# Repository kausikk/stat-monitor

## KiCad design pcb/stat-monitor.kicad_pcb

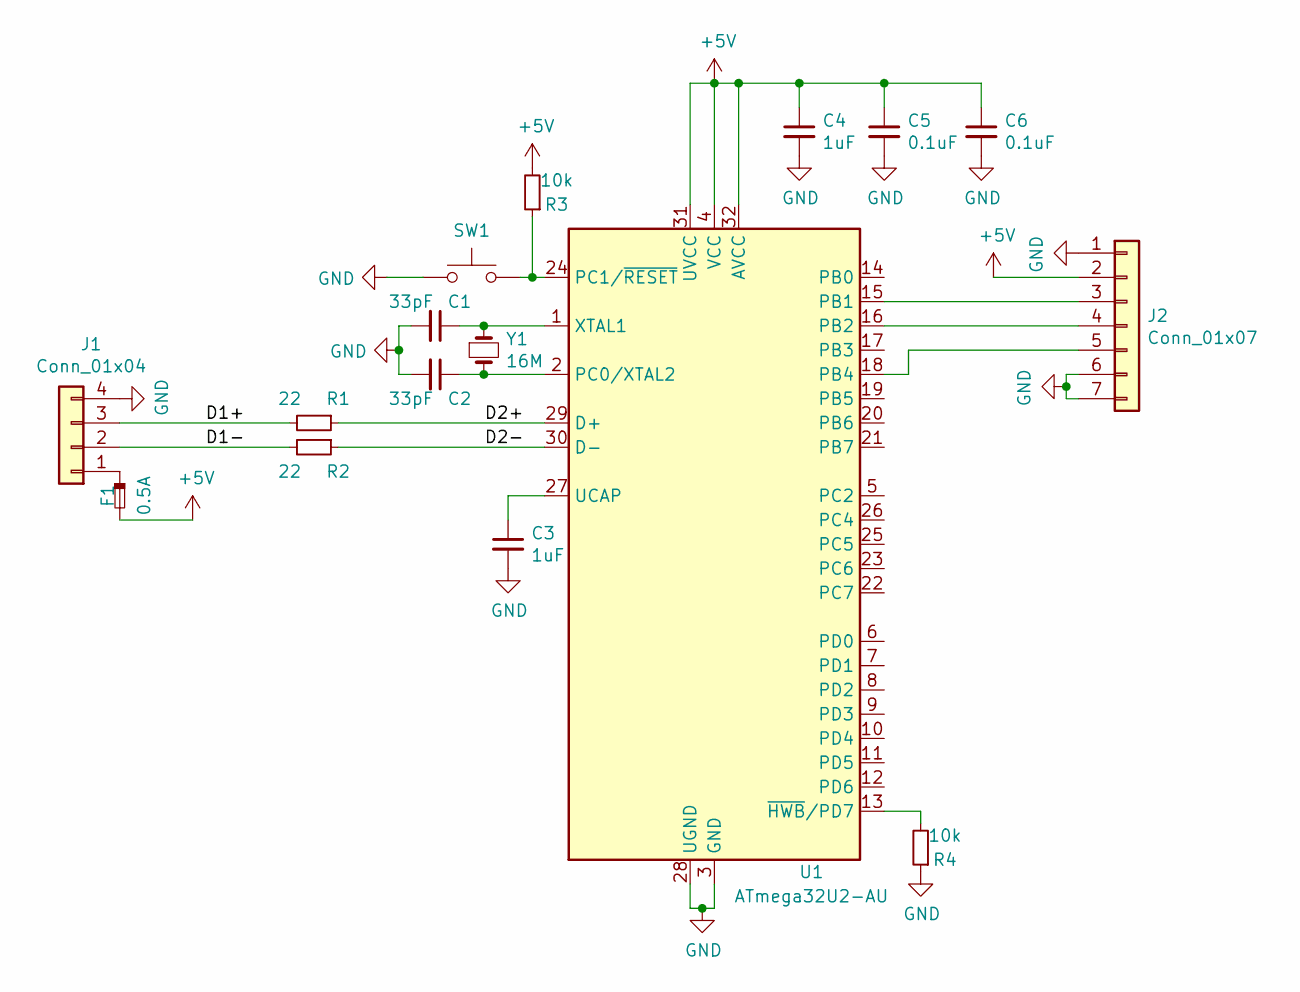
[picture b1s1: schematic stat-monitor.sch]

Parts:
C1, C2: 33pF; C_0603_1608Metric_Pad1.08x0.95mm_HandSolder
C3, C4: 1uF; C_0603_1608Metric_Pad1.08x0.95mm_HandSolder
C5, C6: 0.1uF; C_0603_1608Metric_Pad1.08x0.95mm_HandSolder
F1: 0.5A; Fuse_1206_3216Metric_Pad1.42x1.75mm_HandSolder
J1: Conn_01x04; PinSocket_1x04_P2.54mm_Vertical
J2: Conn_01x07; PinHeader_1x07_P2.54mm_Vertical
R1, R2: 22; R_0603_1608Metric_Pad0.98x0.95mm_HandSolder
R3, R4: 10k; R_0603_1608Metric_Pad0.98x0.95mm_HandSolder
SW1: SW_Push; R_0805_2012Metric_Pad1.20x1.40mm_HandSolder
U1: ATmega32U2-AU; TQFP-32_7x7mm_P0.8mm
Y1: 16M; ECS-160-20-46X

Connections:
+5V: C4.1, C5.1, C6.1, F1.2, J2.2, R3.2, U1.4 (VCC), U1.31 (UVCC), U1.32 (AVCC)
/D1+: J1.3, R1.2
/D1-: J1.2, R2.2
/D2+: R1.1, U1.29 (D+)
/D2-: R2.1, U1.30 (D-)
GND: C1.2, C2.2, C3.2, C4.2, C5.2, C6.2, J1.4, J2.1, J2.6, J2.7, R4.1, SW1.1, U1.3 (GND), U1.28 (UGND)
unnamed: C1.1, U1.1 (XTAL1), Y1.1
unnamed: C2.1, U1.2 (PC0/XTAL2), Y1.2
unnamed: C3.1, U1.27 (UCAP)
unnamed: F1.1, J1.1
unnamed: J2.3, U1.15 (PB1)
unnamed: J2.4, U1.16 (PB2)
unnamed: J2.5, U1.18 (PB4)
unnamed: R3.1, SW1.2, U1.24 (PC1/~RESET)
unnamed: R4.2, U1.13 (~HWB~/PD7)

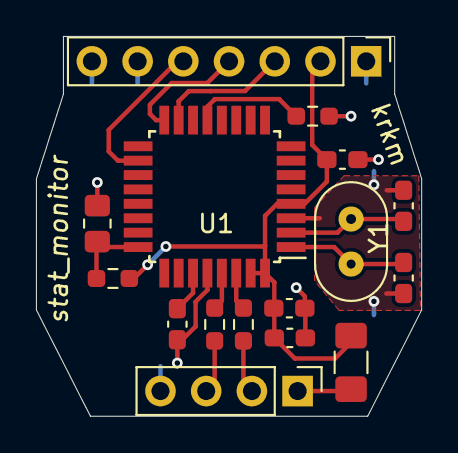
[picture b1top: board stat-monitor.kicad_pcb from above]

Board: 2 copper layers, 21.4 x 21.1 mm, 16 parts (0 on the bottom side), 15 nets.

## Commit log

2021-08-10 Added finalized PCB, initial firmware
2021-08-10 Fixed tabs
2021-08-10 Fixed more tabs
2021-08-10 Refactored some #includes
2021-08-13 Added .net application
2021-08-14 Made some firmware optimizations
2021-08-14 Updated Vendor ID and Product ID
2021-08-15 Implemented stat reading and writing to usb device, added comments
